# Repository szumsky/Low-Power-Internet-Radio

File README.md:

# Low-Power-Internet-Radio
projekt badawczy 22/23

na razie puściutko

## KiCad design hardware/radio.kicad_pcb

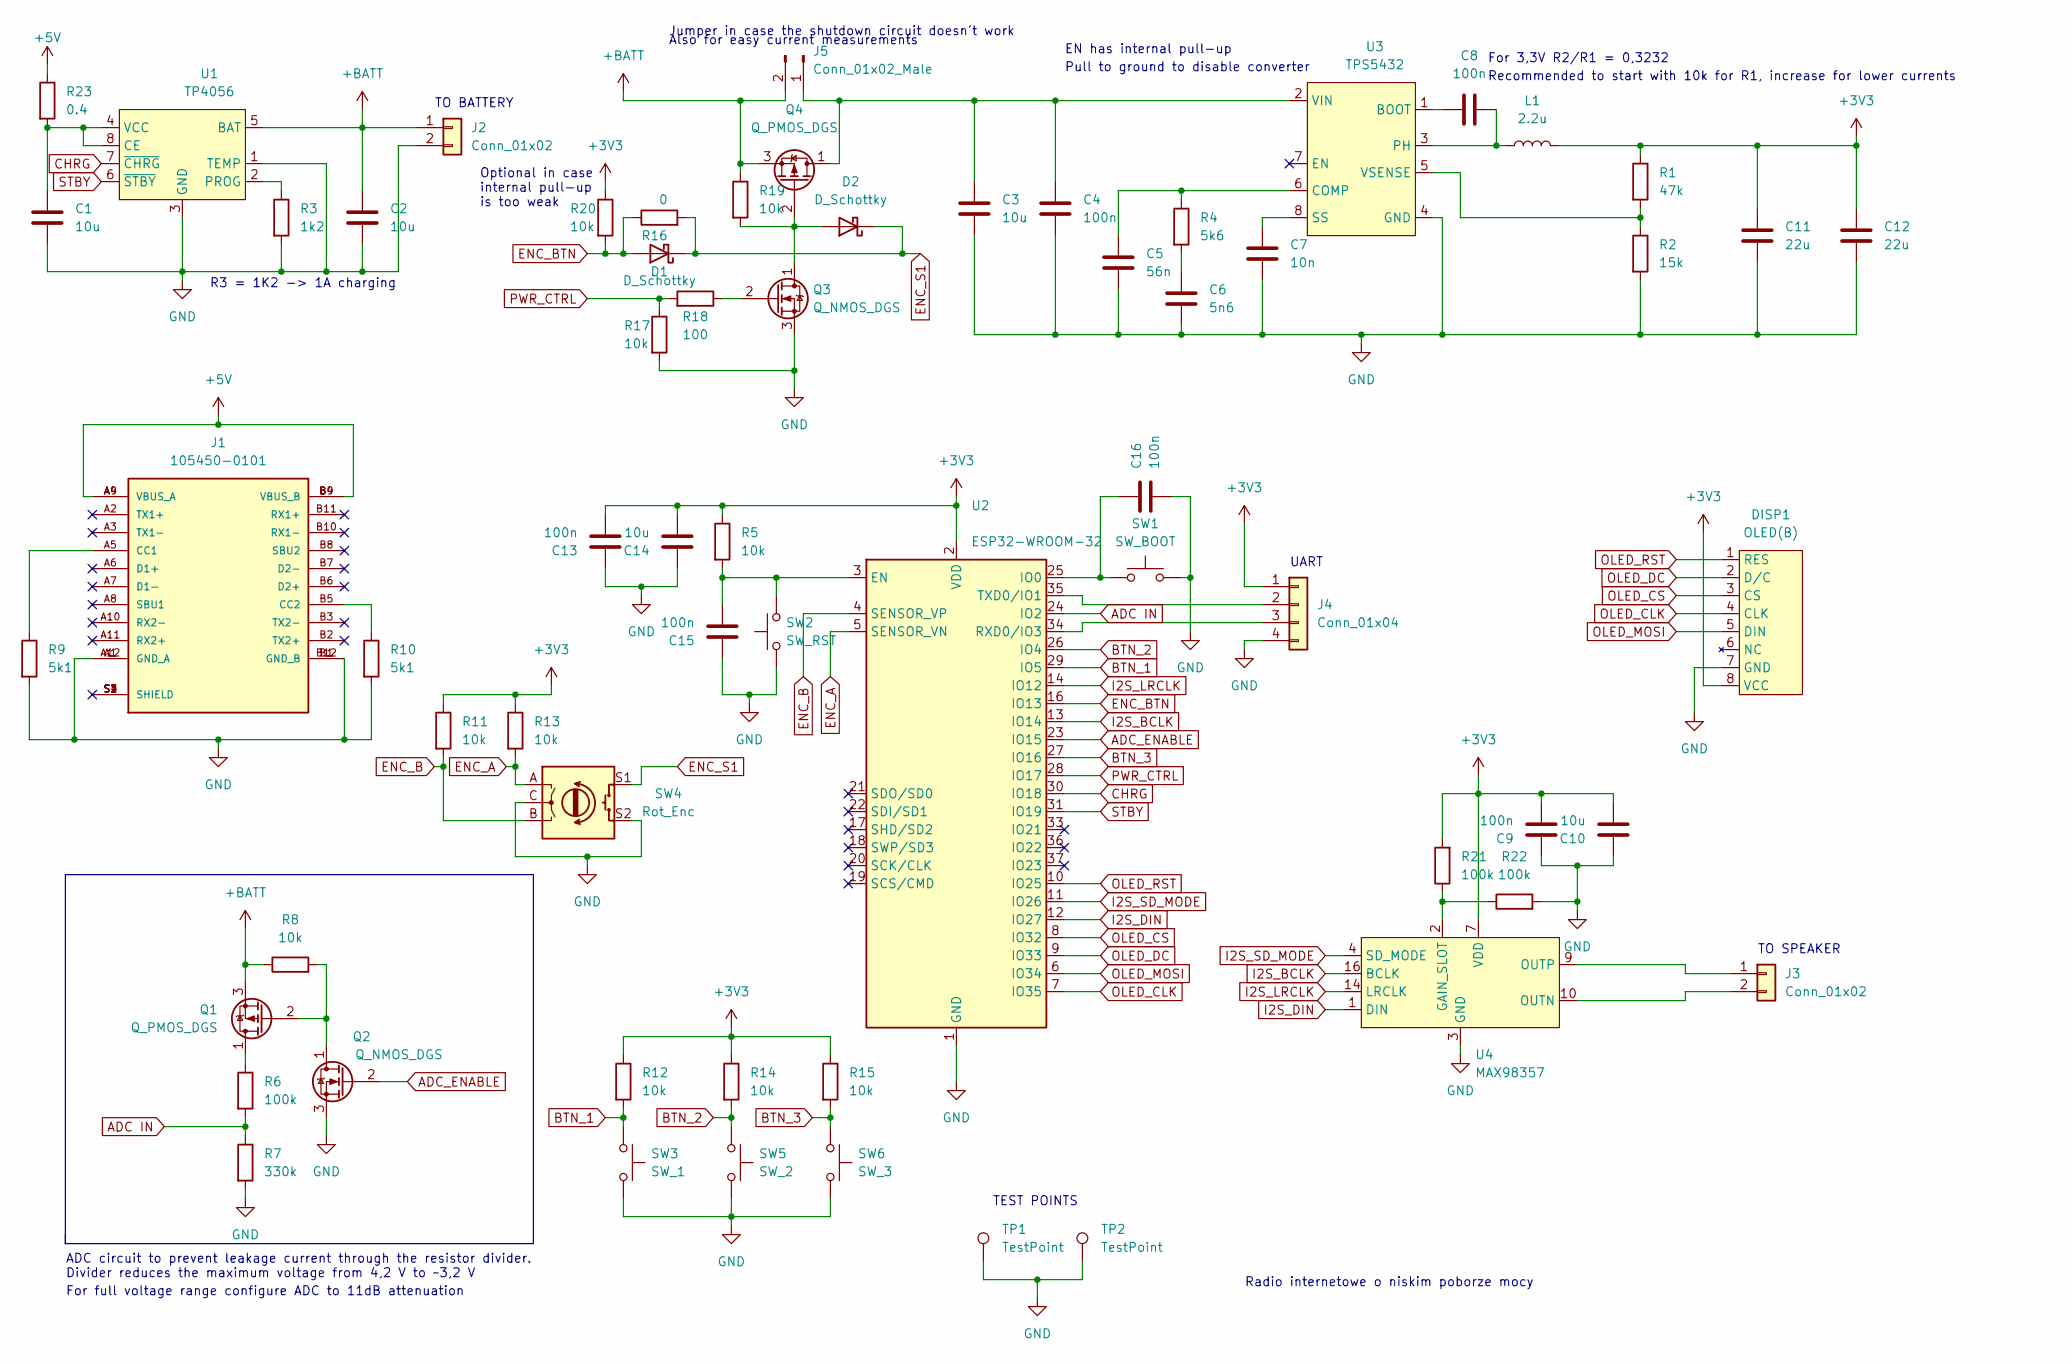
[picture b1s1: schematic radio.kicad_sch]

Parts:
C1, C2, C3, C10, C14: 10u; C_1206_3216Metric
C4, C9, C13, C15, C16: 100n; C_0603_1608Metric
C5: 56n; C_0603_1608Metric
C6: 5n6; C_0603_1608Metric
C7: 10n; C_0603_1608Metric
C8: 100n; C_0603_1608Metric; Voltage rating >10V
C11, C12: 22u; C_1206_3216Metric
D1, D2: D_Schottky; D_SMA
DISP1: OLED(B); waveshare_oled
J1: 105450-0101; MOLEX_105450-0101; PARTREV A7
J2, J3: Conn_01x02; PinHeader_1x02_P2.54mm_Vertical
J4: Conn_01x04; PinHeader_1x04_P2.54mm_Vertical
J5: Conn_01x02_Male; PinHeader_1x02_P2.54mm_Horizontal
L1: 2.2u; DJNR6028-2R2-S
Q1, Q4: Q_PMOS_DGS; SOT-23
Q2, Q3: Q_NMOS_DGS; SOT-23
R1: 47k; R_0603_1608Metric
R2: 15k; R_0603_1608Metric
R3: 1k2; R_0603_1608Metric
R4: 5k6; R_0603_1608Metric
R5, R8, R11, R12, R13, R14, R15, R17, R19, R20: 10k; R_0603_1608Metric
R6, R21, R22: 100k; R_0603_1608Metric
R7: 330k; R_0603_1608Metric
R9, R10: 5k1; R_0603_1608Metric
R16: 0; R_0603_1608Metric
R18: 100; R_0603_1608Metric
R23: 0.4; R_1210_3225Metric; Power rating 0.5 W
SW1: SW_BOOT; SW_Push_1P1T_NO_6x6mm_H9.5mm
SW2: SW_RST; SW_Push_1P1T_NO_6x6mm_H9.5mm
SW3: SW_1; SW_Push_1P1T_NO_6x6mm_H9.5mm
SW4: Rot_Enc; RotaryEncoder_Alps_EC12E-Switch_Vertical_H20mm_CircularMoun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
SW5: SW_2; SW_Push_1P1T_NO_6x6mm_H9.5mm
SW6: SW_3; SW_Push_1P1T_NO_6x6mm_H9.5mm
TP1, TP2: TestPoint; TestPoint_Loop_D2.50mm_Drill1.0mm
U1: TP4056; SOP-8-1EP_4.57x4.57mm_P1.27mm_EP4.57x4.45mm
U2: ESP32-WROOM-32
U3: TPS5432; TI_SO-PowerPAD-8
U4: MAX98357; TQFN-16-1EP_3x3mm_P0.5mm_EP1.23x1.23mm

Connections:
+3V3: C9.2, C10.2, C11.1, C12.1, C13.2, C14.2, DISP1.8 (VCC), J4.1, L1.2, R1.1, R5.1, R11.1, R12.1, R13.1, R14.1, R15.1, R20.1, R21.2, U2.2 (VDD), U4.7 (VDD)
+5V: J1.A4 (VBUS_A), J1.A9 (VBUS_A), J1.B4 (VBUS_B), J1.B9 (VBUS_B), R23.1
+BATT: C2.1, J2.1, J5.2, Q1.3 (S), Q4.3 (S), R8.1, R19.1, U1.5 (BAT)
ADC IN: R6.2, R7.1, U2.24 (IO2)
ADC_ENABLE: Q2.2 (G), U2.23 (IO15)
BTN_1: R12.2, SW3.1, U2.29 (IO5)
BTN_2: R14.2, SW5.1, U2.26 (IO4)
BTN_3: R15.2, SW6.1, U2.27 (IO16)
CHRG: U1.7 (~CHRG), U2.30 (IO18)
ENC_A: R13.2, SW4.A, U2.5 (SENSOR_VN)
ENC_B: R11.2, SW4.B, U2.4 (SENSOR_VP)
ENC_BTN: D1.2 (A), R16.1, R20.2, U2.16 (IO13)
ENC_S1: D1.1 (K), D2.1 (K), R16.2, SW4.S1
GND: C1.2, C2.2, C3.2, C4.2, C5.2, C6.2, C7.2, C9.1, C10.1, C11.2, C12.2, C13.1, C14.1, C15.1, C16.2, DISP1.7 (GND), J1.A1 (GND_A), J1.A12 (GND_A), J1.B1 (GND_B), J1.B12 (GND_B), J2.2, J4.4, Q2.3 (S), Q3.3 (S), R2.2, R3.2, R7.2, R9.2, R10.2, R17.2, R22.2, SW1.2, SW2.1, SW3.2, SW4.C, SW4.S2, SW5.2, SW6.2, TP1.1, TP2.1, U1.1 (TEMP), U1.3 (GND), U1.9, U2.1 (GND), U2.15 (GND), U2.38 (GND), U2.39 (GND), U3.4 (GND), U3.9, U4.3 (GND), U4.17
I2S_BCLK: U2.13 (IO14), U4.16 (BCLK)
I2S_DIN: U2.12 (IO27), U4.1 (DIN)
I2S_LRCLK: U2.14 (IO12), U4.14 (LRCLK)
I2S_SD_MODE: U2.11 (IO26), U4.4 (SD_MODE)
unnamed: C1.1, R23.2, U1.4 (VCC), U1.8 (CE)
unnamed: C3.1, C4.1, J5.1, Q4.1 (D), U3.2 (VIN)
unnamed: C5.1, R4.1, U3.6 (COMP)
unnamed: C6.1, R4.2
unnamed: C7.1, U3.8 (SS)
unnamed: C8.1, L1.1, U3.3 (PH)
unnamed: C8.2, U3.1 (BOOT)
unnamed: C15.2, R5.2, SW2.2, U2.3 (EN)
unnamed: C16.1, SW1.1, U2.25 (IO0)
unnamed: D2.2 (A), Q3.1 (D), Q4.2 (G), R19.2
unnamed: J1.A5 (CC1), R9.1
unnamed: J1.B5 (CC2), R10.1
unnamed: J3.1, U4.9 (OUTP)
unnamed: J3.2, U4.10 (OUTN)
unnamed: J4.2, U2.35 (TXD0/IO1)
unnamed: J4.3, U2.34 (RXD0/IO3)
unnamed: Q1.1 (D), R6.1
unnamed: Q1.2 (G), Q2.1 (D), R8.2
unnamed: Q3.2 (G), R18.1
unnamed: R1.2, R2.1, U3.5 (VSENSE)
unnamed: R3.1, U1.2 (PROG)
unnamed: R21.1, R22.1, U4.2 (GAIN_SLOT)
OLED_CLK: DISP1.4 (CLK), U2.7 (IO35)
OLED_CS: DISP1.3 (CS), U2.8 (IO32)
OLED_DC: DISP1.2 (D/C), U2.9 (IO33)
OLED_MOSI: DISP1.5 (DIN), U2.6 (IO34)
OLED_RST: DISP1.1 (RES), U2.10 (IO25)
PWR_CTRL: R17.1, R18.2, U2.28 (IO17)
STBY: U1.6 (~STBY), U2.31 (IO19)

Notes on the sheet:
Jumper in case the shutdown circuit doesn't work
Radio internetowe o niskim poborze mocy
Optional in case internal pull-up is too weak
TO BATTERY
ADC circuit to prevent leakage current through the resistor divider. Divider reduces the maximum voltage from 4,2 V to ~3,2 V
For full voltage range configure ADC to 11dB attenuation
Pull to ground to disable converter
Recommended to start with 10k for R1, increase for lower currents
R3 = 1K2 -> 1A charging
EN has internal pull-up
TEST POINTS
Also for easy current measurements
TO SPEAKER
For 3,3V R2/R1 = 0,3232
UART

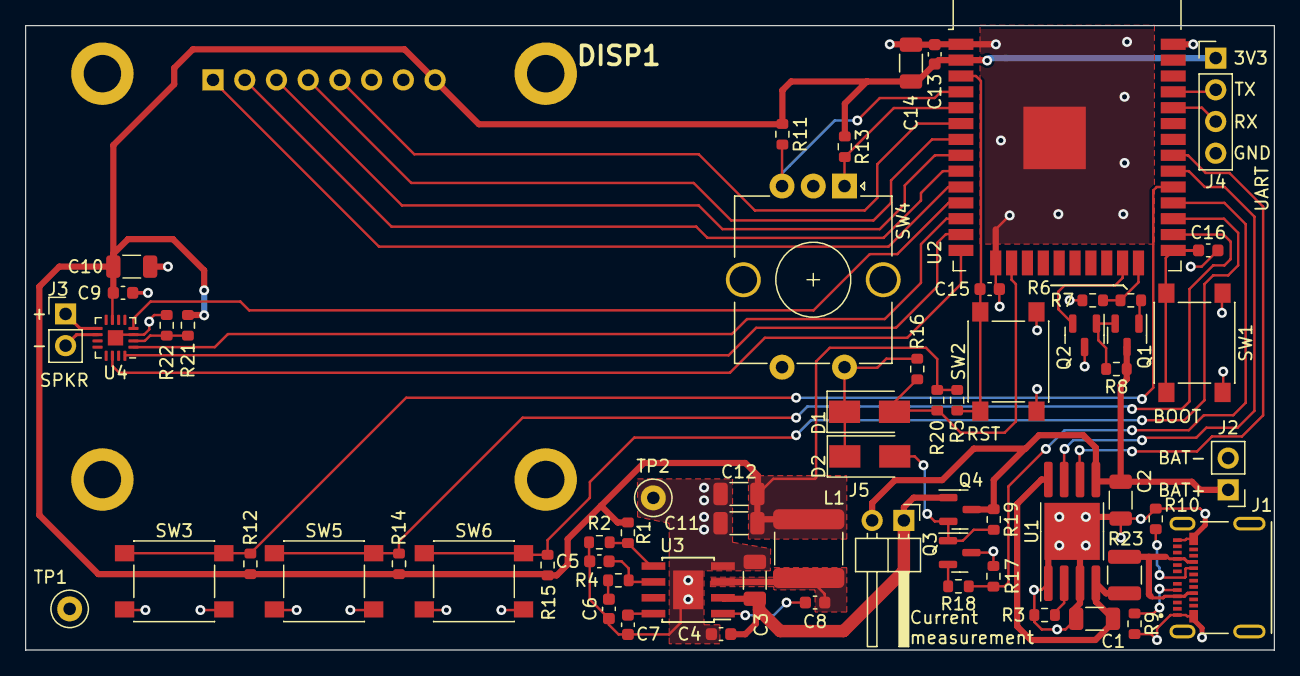
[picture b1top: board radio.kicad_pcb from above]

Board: 2 copper layers, 100.0 x 50.0 mm, 64 parts (0 on the bottom side), 47 nets.

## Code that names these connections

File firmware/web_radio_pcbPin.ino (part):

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
//Digital I/O used  //Makerfabs Audio V2.0
#define I2S_DOUT   27  //27 //orange pi 40
#define I2S_BCLK   14  //26 //yellow pi 12
#define I2S_LRC    12  //25 //green  pi 35
#define AMPON      26  //13 //amp on blue pi 22

#define OLED_MOSI  23  //23
#define OLED_CLK   22  //18
#define OLED_DC    33  //16
#define OLED_CS    32  //5
#define OLED_RST   25  //17

#define LED 2
#define PWR_CTRL 17

#define ADC_IN          34//2
#define ADC_ENABLE      15
#define batteryCharge   18
#define batteryStandby  19

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volatile int enc = 0;
volatile int encTemp = 0;
volatile int encBtn = 0;
const int Pin_enc_a       =   39; //35;
const int Pin_enc_b       =   36; //32;
const int Pin_enc_btn     =   13; //34;

//button variables
volatile int btnLeft;
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void setup()
{
    //IO mode init
    pinMode(Pin_enc_a,      INPUT_PULLUP);
    pinMode(Pin_enc_b,      INPUT_PULLUP);
    pinMode(Pin_enc_btn,    INPUT_PULLUP);
    pinMode(Pin_btn_left,   INPUT_PULLUP);
    pinMode(Pin_btn_center, INPUT_PULLUP);
    pinMode(Pin_btn_right,  INPUT_PULLUP);
    pinMode(AMPON, OUTPUT);
    pinMode(PWR_CTRL, OUTPUT);
    pinMode(0, INPUT_PULLUP);
    pinMode(34, INPUT);
    pinMode(15, OUTPUT);
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    digitalWrite(15, LOW);

    //ISR
    //attachInterrupt(digitalPinToInterrupt(Pin_enc_a),      ENC_ISR,        FALLING);
    attachInterrupt(digitalPinToInterrupt(Pin_enc_btn),    ENC_BTN_ISR,    FALLING);
    attachInterrupt(digitalPinToInterrupt(Pin_btn_left),   BTN_LEFT_ISR,   FALLING);
    attachInterrupt(digitalPinToInterrupt(Pin_btn_center), BTN_CENTER_ISR, FALLING);
    attachInterrupt(digitalPinToInterrupt(Pin_btn_right),  BTN_RIGHT_ISR,  FALLING);
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    display.setCursor(0, 0);

    //Audio(I2S)
    audio.setPinout(I2S_BCLK, I2S_LRC, I2S_DOUT);
    audio.setVolume(volume); // 0...21 

    //enable wake up sources
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void checkLongPress() 
{
  // read the state of the switch/button:
  currentState = digitalRead(Pin_enc_btn);

  if(lastState == HIGH && currentState == LOW) {        // button is pressed
    pressedTime = millis();
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
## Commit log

2022-04-26 dodano foldery dzielące na arduino i esp-idf
2022-04-28 Wrzucone arduino
2022-04-29 Część sieciowa interfejsu użytkownika
    Metody Wyszukiwania sieci, Wpisywania hasła przy pomocy przycisków i enkodera, logowanie do sieci WiFi.
2022-04-29 Kod odbiornika radia internetowego
    Dodano obsługę wyświetlacza oraz zmianę głośności za pomocą przycisków.
2022-06-10 dodano hardware
2022-06-10 stworzono projekt hardware
2022-06-10 stworzony symbol MAX98357
2022-06-10 dodany symbol TP4056
2022-06-10 utworzono symbol TPS5432
2022-06-10 dodano ESP32-WROOM-32 na schemacie
2022-06-11 stworzono symbol waveshare OLED
2022-06-11 aktualizacja opisu symbolu OLED
2022-06-11 aktualizacja opisu symbolu OLED (tym razem na prawde)
2022-06-11 stworzono footprint wyswietlacza oled
2022-06-11 przypisano footprint wyswietlacza do symbolu
2022-06-11 NETy zasilania i routing TP4056
2022-08-20 schematic
2022-08-21 added reference
2022-08-22 added to schematic: rotary encoder, buttons, USB-C receptacle CC resistors
2022-08-22 remove zip file
2022-08-25 added shutdown circuit
2022-08-25 comments
2022-08-27 began placement
2022-08-27 placement
2022-08-29 placement (possibly close to final)
2022-08-29 placement and some routing
2022-08-31 routing
2022-09-02 board finished (?)
2022-09-04 fixed DRC violations, added silkscreen legend
2022-09-17 made oled mounting point pads bigger
2022-10-16 Fixed C8 connection from BOOT-GND to BOOT-PH
2022-10-16 Added 0.4 ohm 0.5 W resistor to TP4056 to help with power dissipation
2022-10-23 adjusted silkscreen and some vias to improve labeling consistency and readability
2022-10-23 added copper fill cutout to the speaker connector and adjusted the 3V3 power trace near it to reduce potential proximity/ground-plane induced crosstalk
2022-10-23 added 'Current measurement' and 'UART' labels to J5 and J4 respectively
2022-10-23 Added project description to bottom silkscreen
2022-10-23 added test points; corrected C5 silkscreen again
2022-10-23 redone DC-DC converter layout to match the reference in datasheet
2022-10-23 removed copper pour on signal layer because Eric Bogatin said so
2023-05-23 Add files via upload
    Arduino code for nvs flash management. Use for hardcoding ssid password pairs and radio stations url.
2023-05-23 Arduino code for nvs flash management. Hardcode ssid, password, radio stations.
2023-05-23 Arduino code for nvs flash management.
    Use for hardcoding ssid password pairs, radio stations.
    Check contents of nvs flash.
2023-05-23 Arduino code for erasing flash
    Use to wipe all data added using preferences library.
2023-05-23 Arduino code for LowPowerESP32WebRadio
    Needs modified version of ESP32AudioI2S library.
2023-05-23 Modified Audio library
2023-05-23 removed irrelevant jumper (J5) comment
2023-05-23 Mark R16 as not mounted
2023-05-23 Added KNOWN_ISSUES.txt and marked known issues on schematic.
2023-05-23 Grammar.
2023-05-23 Added OLED module link to symbol.
